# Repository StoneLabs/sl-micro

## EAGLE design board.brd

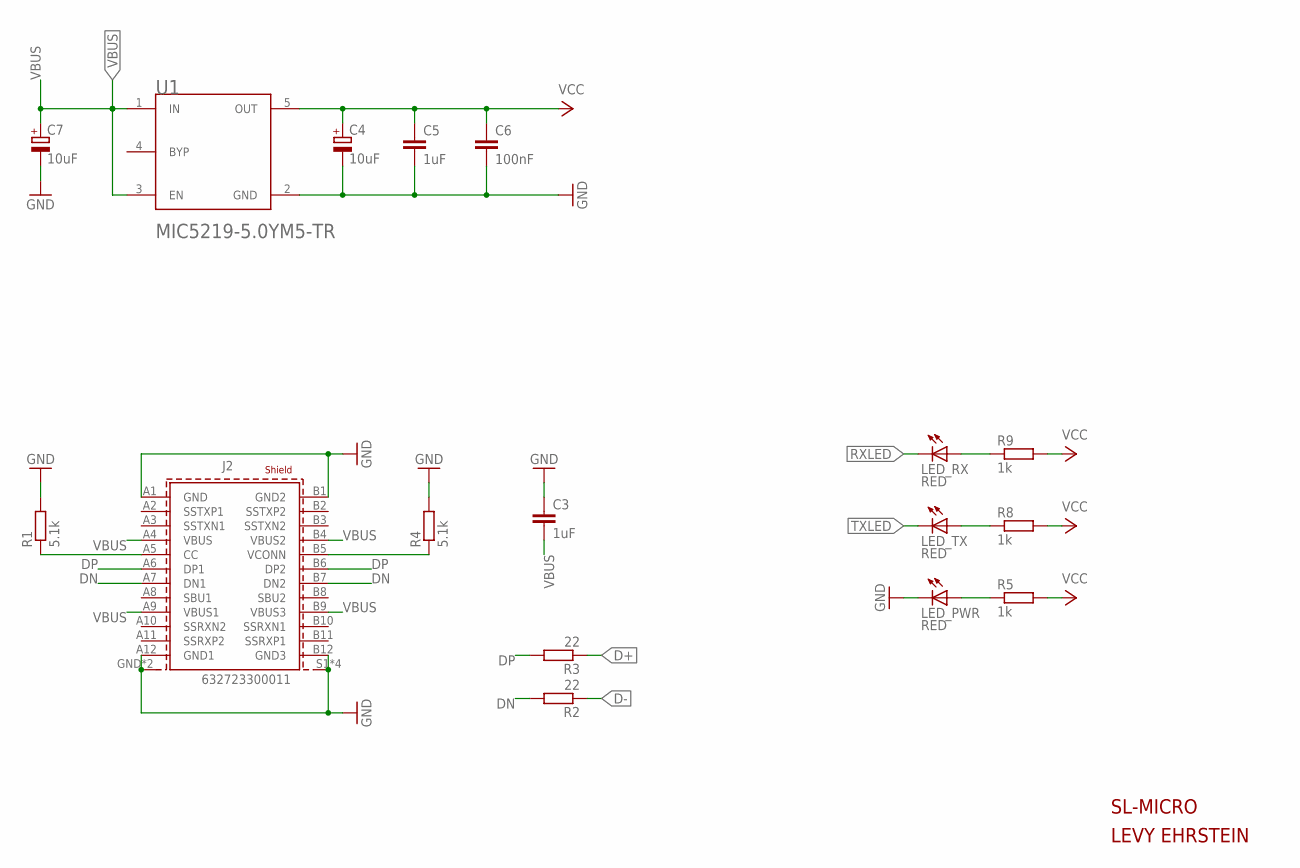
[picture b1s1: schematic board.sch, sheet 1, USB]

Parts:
C3, C5: 1uF; C0805
C4, C7: 10uF; SMC_B
C6: 100nF; C0805
J2: 632723300011
LED_PWR: RED; CHIP-LED0805
LED_RX: RED; CHIP-LED0805
LED_TX: RED; CHIP-LED0805
R1, R4: 5.1k; R0805
R2, R3: 22; R0805
R5, R8, R9: 1k; R0805
U1: MICROCHIP_TECHNOLOGY_MIC5219-5_0YM5-TRMICROCHIP_T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; MICROCHIP_TECHNOLOGY_MIC5219-5_0YM5-TR_0

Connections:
D+: R3.1; also elsewhere on the board
D-: R2.1; also elsewhere on the board
DN: J2.A7 (DN1), J2.B7 (DN2), R2.2
DP: J2.A6 (DP1), J2.B6 (DP2), R3.2
GND: C3.1, C4.-, C5.2, C6.2, C7.-, J2.A1 (GND), J2.A12 (GND1), J2.B1 (GND2), J2.B12 (GND3), J2.GND (SHIELD), J2.GND1 (SHIELD), J2.S1 (SHIELD1), J2.S2 (SHIELD1), J2.S3 (SHIELD1), J2.S4 (SHIELD1), LED_PWR.C, R1.2, R4.2, U1.2 (GND); also elsewhere on the board
unnamed: J2.A5 (CC), R1.1
unnamed: J2.B5 (VCONN), R4.1
unnamed: LED_PWR.A, R5.1
unnamed: LED_TX.A, R8.1
unnamed: LED_RX.A, R9.1
RXLED: LED_RX.C; also elsewhere on the board
TXLED: LED_TX.C; also elsewhere on the board
VBUS: C3.2, C7.+, J2.A4 (VBUS), J2.A9 (VBUS1), J2.B4 (VBUS2), J2.B9 (VBUS3), U1.1 (IN), U1.3 (EN); also elsewhere on the board
VCC: C4.+, C5.1, C6.1, R5.2, R8.2, R9.2, U1.5 (OUT); also elsewhere on the board

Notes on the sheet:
SL-MICRO
LEVY EHRSTEIN

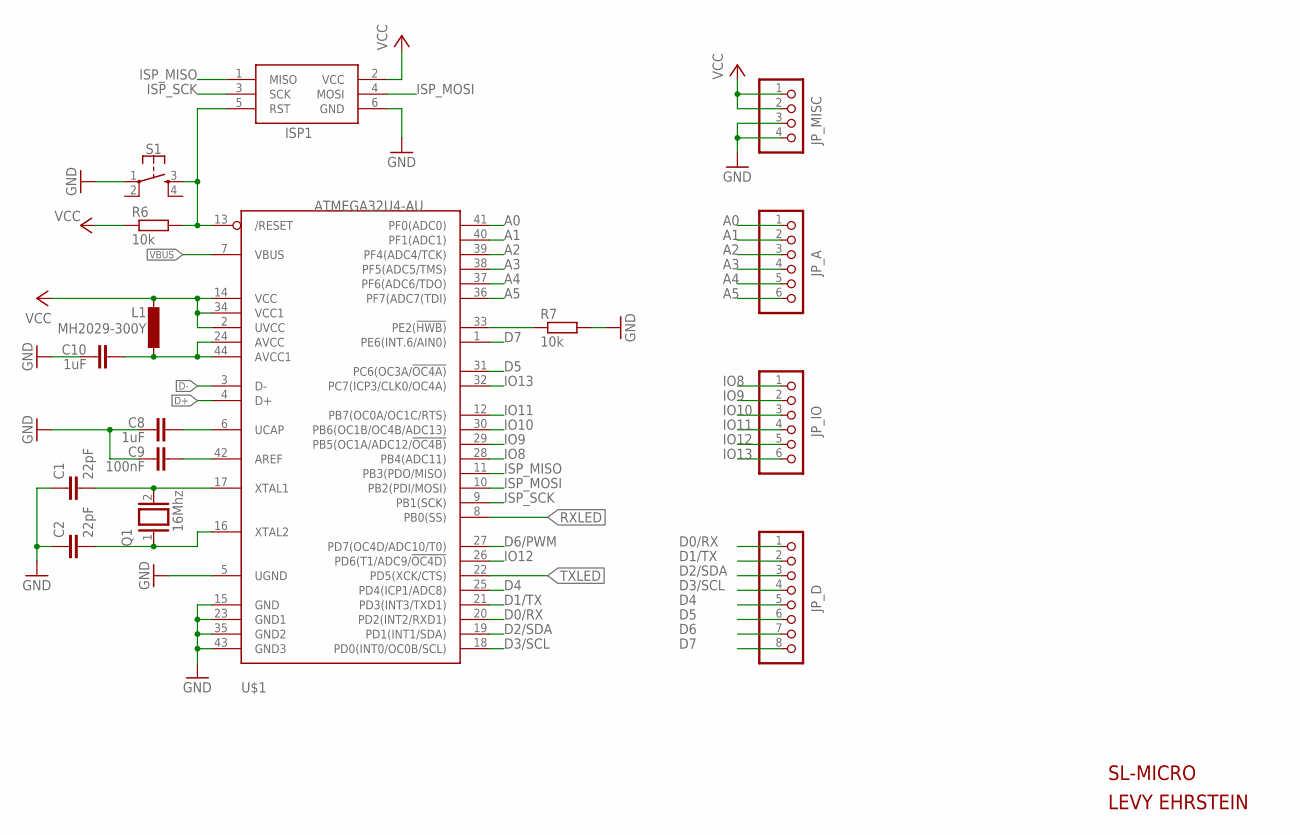
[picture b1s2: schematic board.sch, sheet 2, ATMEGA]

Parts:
C1, C2: 22pF; C0805
C8, C10: 1uF; C0805
C9: 100nF; C0805
ISP1: AVRISP-6; AVRISP
JP_A: PINHD-1X6; 1X06
JP_D: PINHD-1X8; 1X08
JP_IO: PINHD-1X6; 1X06
JP_MISC: PINHD-1X4; 1X04
L1: MH2029-300Y; L2012C
Q1: 16Mhz; QS
R6, R7: 10k; R0805
S1: MOMENTARY-SWITCH-SPST-2-SMD-4.6X2.8MM; TACTILE_SWITCH_SMD_4.6X2.8MM
U$1: ATMEGA32U4-AU; TQFP44

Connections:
A0: JP_A.1, U$1.41 (PF0(ADC0))
A1: JP_A.2, U$1.40 (PF1(ADC1))
A2: JP_A.3, U$1.39 (PF4(ADC4/TCK))
A3: JP_A.4, U$1.38 (PF5(ADC5/TMS))
A4: JP_A.5, U$1.37 (PF6(ADC6/TDO))
A5: JP_A.6, U$1.36 (PF7(ADC7(TDI))
D0/RX: JP_D.1, U$1.20 (PD2(INT2/RXD1))
D1/TX: JP_D.2, U$1.21 (PD3(INT3/TXD1))
D2/SDA: JP_D.3, U$1.19 (PD1(INT1/SDA))
D3/SCL: JP_D.4, U$1.18 (PD0(INT0/OC0B/SCL))
D4: JP_D.5, U$1.25 (PD4(ICP1/ADC8))
D5: JP_D.6, U$1.31 (PC6(OC3A/!OC4A))
D6: JP_D.7
D6/PWM: U$1.27 (PD7(OC4D/ADC10/T0))
D7: JP_D.8, U$1.1 (PE6(INT.6/AIN0))
D+: U$1.4 (D+); also elsewhere on the board
D-: U$1.3 (D-); also elsewhere on the board
GND: C1.1, C2.1, C8.1, C9.1, C10.1, ISP1.6 (GND), JP_MISC.3, JP_MISC.4, R7.2, S1.1, U$1.5 (UGND), U$1.15 (GND), U$1.23 (GND1), U$1.35 (GND2), U$1.43 (GND3); also elsewhere on the board
IO8: JP_IO.1, U$1.28 (PB4(ADC11))
IO9: JP_IO.2, U$1.29 (PB5(OC1A/ADC12/!OC4B))
IO10: JP_IO.3, U$1.30 (PB6(OC1B/OC4B/ADC13))
IO11: JP_IO.4, U$1.12 (PB7(OC0A/OC1C/RTS))
IO12: JP_IO.5, U$1.26 (PD6(T1/ADC9/!OC4D))
IO13: JP_IO.6, U$1.32 (PC7(ICP3/CLK0/OC4A))
ISP_MISO: ISP1.1 (MISO), U$1.11 (PB3(PDO/MISO))
ISP_MOSI: ISP1.4 (MOSI), U$1.10 (PB2(PDI/MOSI))
ISP_SCK: ISP1.3 (SCK), U$1.9 (PB1(SCK))
unnamed: C2.2, Q1.1, U$1.16 (XTAL2)
unnamed: ISP1.5 (RST), R6.2, S1.3, U$1.13 (/RESET)
unnamed: C8.2, U$1.6 (UCAP)
unnamed: C1.2, Q1.2, U$1.17 (XTAL1)
unnamed: C9.2, U$1.42 (AREF)
unnamed: C10.2, L1.1, U$1.24 (AVCC), U$1.44 (AVCC1)
unnamed: R7.1, U$1.33 (PE2(!HWB))
RXLED: U$1.8 (PB0(SS)); also elsewhere on the board
TXLED: U$1.22 (PD5(XCK/CTS)); also elsewhere on the board
VBUS: U$1.7 (VBUS); also elsewhere on the board
VCC: ISP1.2 (VCC), JP_MISC.1, JP_MISC.2, L1.2, R6.1, U$1.2 (UVCC), U$1.14 (VCC), U$1.34 (VCC1); also elsewhere on the board

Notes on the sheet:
SL-MICRO
LEVY EHRSTEIN

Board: 2 copper layers, 33 parts (0 on the bottom side), 43 nets, no tracks yet.

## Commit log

2020-10-08 Add USB-C Connector, VCC from bus
2020-10-08 Add reset switch; Minor cleanup
2020-10-09 Add connections for AtMega32u4
2020-10-13 Add ISP-6 Header
2020-11-05 Add Analog and Digital IO header
2020-11-09 Finish header; Add RX/TX LEDs
2020-11-09 Add frames to sheets
2020-12-04 Add WIP initial PCB placements

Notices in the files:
parts and their libraries:
Wurth_Connectors_WR-USB: Copyright: Würth Elektronik
SparkFun-Switches: Licensing: Creative Commons ShareAlike 4.0 International - https://creativecommons.org/licenses/by-sa/4.0
